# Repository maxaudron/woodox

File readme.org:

#+title: Readme

* Decisions
** MUX controll central vs seperate
We can either control each mux on it's own, taking up significantly more pins
or have them be controlled all at the same time

- Much simpler routing
- less traces

- customize matrix scanning

** Split vs Lefty logic
either controller on each hand, or controller only on one hand

*** Split
- can use more mux
- lower latency?
- more keys
- mirror PCB

CD74HC4051
  
*** Lefty
- less cost
- simpler?
- analog signals over longer wire
  - potential interference?

- sepperate PCB designs
  
* TODOs
** TODO connect mux com only to uneven GPIO pins for PWM input
** DONE add pull up resistors to mux com
** DONE adjust value of drv5057
A3 uses ~25% of the messuring range in one direction
A2 would use ~50%
A1 would use 100%, but might clip.
** DONE switch to drv5056A2
** TODO Use same pins for all mux selects
** TODO matrix to keycode conversion
** TODO usb hid impl
https://github.com/dlkj/usbd-human-interface-device

* Magnet distance lookup table
3.25V VCC
3.00V @ 2.25mm = 24.12mT
0.95V @ 6.25mm =  3.52mT

#+begin_src python :python3.10 :results output
import math

R = 1.75
D = 4
z = 2.25
r = 24.12
B = - ( (2*r) / ( ( z / math.sqrt( (R**2) + (z**2) )) - ( (D+z) / math.sqrt( (R**2) + ((D+z)**2) ) ) ) )
print(B)
#+end_src

#+RESULTS:
: 277.8612937046934

** lookup table
#+begin_src python :python python3.10 :results output
import math
import numpy as np

Z = np.linspace(0.1, 10, 100)
B = 0.38
R = 1.75
D = 4

def flux(z):
    return (((B/2)*( ( (D+z) / math.sqrt((R**2) + ((D+z)**2)) )  -  ( z / math.sqrt((R**2)+(z**2)) )))*1000)

def voltage(x):
    return (600 + x * (100))

def value(x):
    return x / (3300.0 / 256.0)

flux_vec = np.vectorize(flux)
voltage_vec = np.vectorize(voltage)
value_vec = np.vectorize(value)

prev = 0
for z in Z:
    z = round(z, 2)
    y = float(flux_vec(z))
    v = float(voltage_vec(y))
    value = float(value_vec(v))
    value = round(value)
    print(str(value) + "..=" + str(prev-1) + " => " + str(int(z * 10)) + ",")
    prev = value
#+end_src

#+RESULTS:
#+begin_example
1318..=-1 => 1,
1240..=1317 => 2,
1163..=1239 => 3,
1088..=1162 => 4,
1015..=1087 => 5,
946..=1014 => 6,
880..=945 => 7,
819..=879 => 8,
761..=818 => 9,
706..=760 => 10,
656..=705 => 11,
610..=655 => 12,
567..=609 => 13,
528..=566 => 14,
492..=527 => 15,
459..=491 => 16,
429..=458 => 17,
401..=428 => 18,
375..=400 => 19,
352..=374 => 20,
331..=351 => 21,
312..=330 => 22,
294..=311 => 23,
277..=293 => 24,
262..=276 => 25,
248..=261 => 26,
236..=247 => 27,
224..=235 => 28,
213..=223 => 29,
203..=212 => 30,
194..=202 => 31,
186..=193 => 32,
178..=185 => 33,
170..=177 => 34,
164..=169 => 35,
157..=163 => 36,
151..=156 => 37,
146..=150 => 38,
141..=145 => 39,
136..=140 => 40,
132..=135 => 41,
127..=131 => 42,
124..=126 => 43,
120..=123 => 44,
116..=119 => 45,
113..=115 => 46,
110..=112 => 47,
107..=109 => 48,
105..=106 => 49,
102..=104 => 50,
100..=101 => 51,
98..=99 => 52,
95..=97 => 53,
93..=94 => 54,
92..=92 => 55,
90..=91 => 56,
88..=89 => 57,
86..=87 => 58,
85..=85 => 59,
83..=84 => 60,
82..=82 => 61,
81..=81 => 62,
79..=80 => 63,
78..=78 => 64,
77..=77 => 65,
76..=76 => 66,
75..=75 => 67,
74..=74 => 68,
73..=73 => 69,
72..=72 => 70,
71..=71 => 71,
71..=70 => 72,
70..=70 => 73,
69..=69 => 74,
68..=68 => 75,
68..=67 => 76,
67..=67 => 77,
66..=66 => 78,
66..=65 => 79,
65..=65 => 80,
65..=64 => 81,
64..=64 => 82,
64..=63 => 83,
63..=63 => 84,
63..=62 => 85,
62..=62 => 86,
62..=61 => 87,
61..=61 => 88,
61..=60 => 89,
60..=60 => 90,
60..=59 => 91,
60..=59 => 92,
59..=59 => 93,
59..=58 => 94,
59..=58 => 95,
58..=58 => 96,
58..=57 => 97,
58..=57 => 98,
58..=57 => 99,
57..=57 => 100,
#+end_example

** graph
#+NAME: magnets
|       B |    R | D |
|---------+------+---|
|    0.38 | 1.75 | 4 |
|    0.28 | 1.75 | 4 |

#+begin_src python :python python3.10 :results file :exports both :var data=magnets
import math
import matplotlib.pyplot as plt
import numpy as np

for line in data:
    Z = np.linspace(0.1, 10, 100)
    B = line[0]
    R = line[1]
    D = line[2]

    def f(z):
        r = (((B/2)*( ( (D+z) / math.sqrt((R**2) + ((D+z)**2)) )  -  ( z / math.sqrt((R**2)+(z**2)) )))*1000)
        if z == 2.0:
            plt.annotate('A=' + str(z) + "," + str(round(r, 2)), xy=(z, r), xytext=(z+1, r+1))
        if z == 6.3:
            plt.annotate('B=' + str(z) + "," + str(round(r, 2)), xy=(z, r), xytext=(z+1, r+1))
        return r

    x = np.vectorize(f)
    plt.plot(Z, x(Z), label="B = " + str(B))

plt.xlabel("mm")
plt.ylabel("mT")
plt.legend()
filename = "plot.png"
plt.savefig(filename)
return(filename)
#+end_src

#+RESULTS:
[[file:plot.png]]

* Parts
LED Controller https://jlcpcb.com/partdetail/3305937-IS31FL3741A_QFLS4TR/C2940604

Multiplexer https://www.ti.com/lit/ds/symlink/cd74hc4067.pdf

Example rp2040 usage https://proto-pic.co.uk/content/RPI-PICO-R3-PUBLIC-SCHEMATIC.pdf

rp2040 https://datasheets.raspberrypi.com/rp2040/rp2040-datasheet.pdf

** Hall Sensor
https://www.ti.com/sensors/magnetic-sensors/linear-hall-effect-sensors/overview.html

DRV5055A3 SOT-23
https://www.ti.com/lit/ds/symlink/drv5055.pdf?ts=1672207827147&ref_url=https%253A%252F%252Fwww.ti.com%252Fproduct%252FDRV5055%252Fpart-details%252FDRV5055A1QLPG

35 keys per side

DRV5057
https://www.ti.com/lit/ds/symlink/drv5057.pdf?ts=1672321537787&ref_url=https%253A%252F%252Fwww.ti.com%252Fsensors%252Fmagnetic-sensors%252Flinear-hall-effect-sensors%252Fproducts.html

https://www.digikey.de/en/product-highlight/s/sunled/reverse-mount-rgb-plcc-smd-led

13,200 Gauss
1320mT

3.5mm diameter x 4 thiccness
z from 2.25mm to 6.25mm

Divide[13200,2](Divide[D + 4mm,Sqrt[Power[\(40)0.5 * 3.5mm\(41),2]+ \(40)D + 4mm\(41)]] - Divide[D,Sqrt[Power[\(40)0.5 * 3.5mm\(41),2]+ Power[D,2]]])

#+begin_src gnuplot
B = 1480
C = 4.7625
T = 12.7

plot [D = -20 :20] (B/2)*( ( ( D + T ) / sqrt( (0.5*C)**2 + (D+T)**2 ) ) - ( D / sqrt(0.5*C)**2 + D**2 ) )
#+end_src

https://crocus-technology.com/basic-magnetic-field-calculator/

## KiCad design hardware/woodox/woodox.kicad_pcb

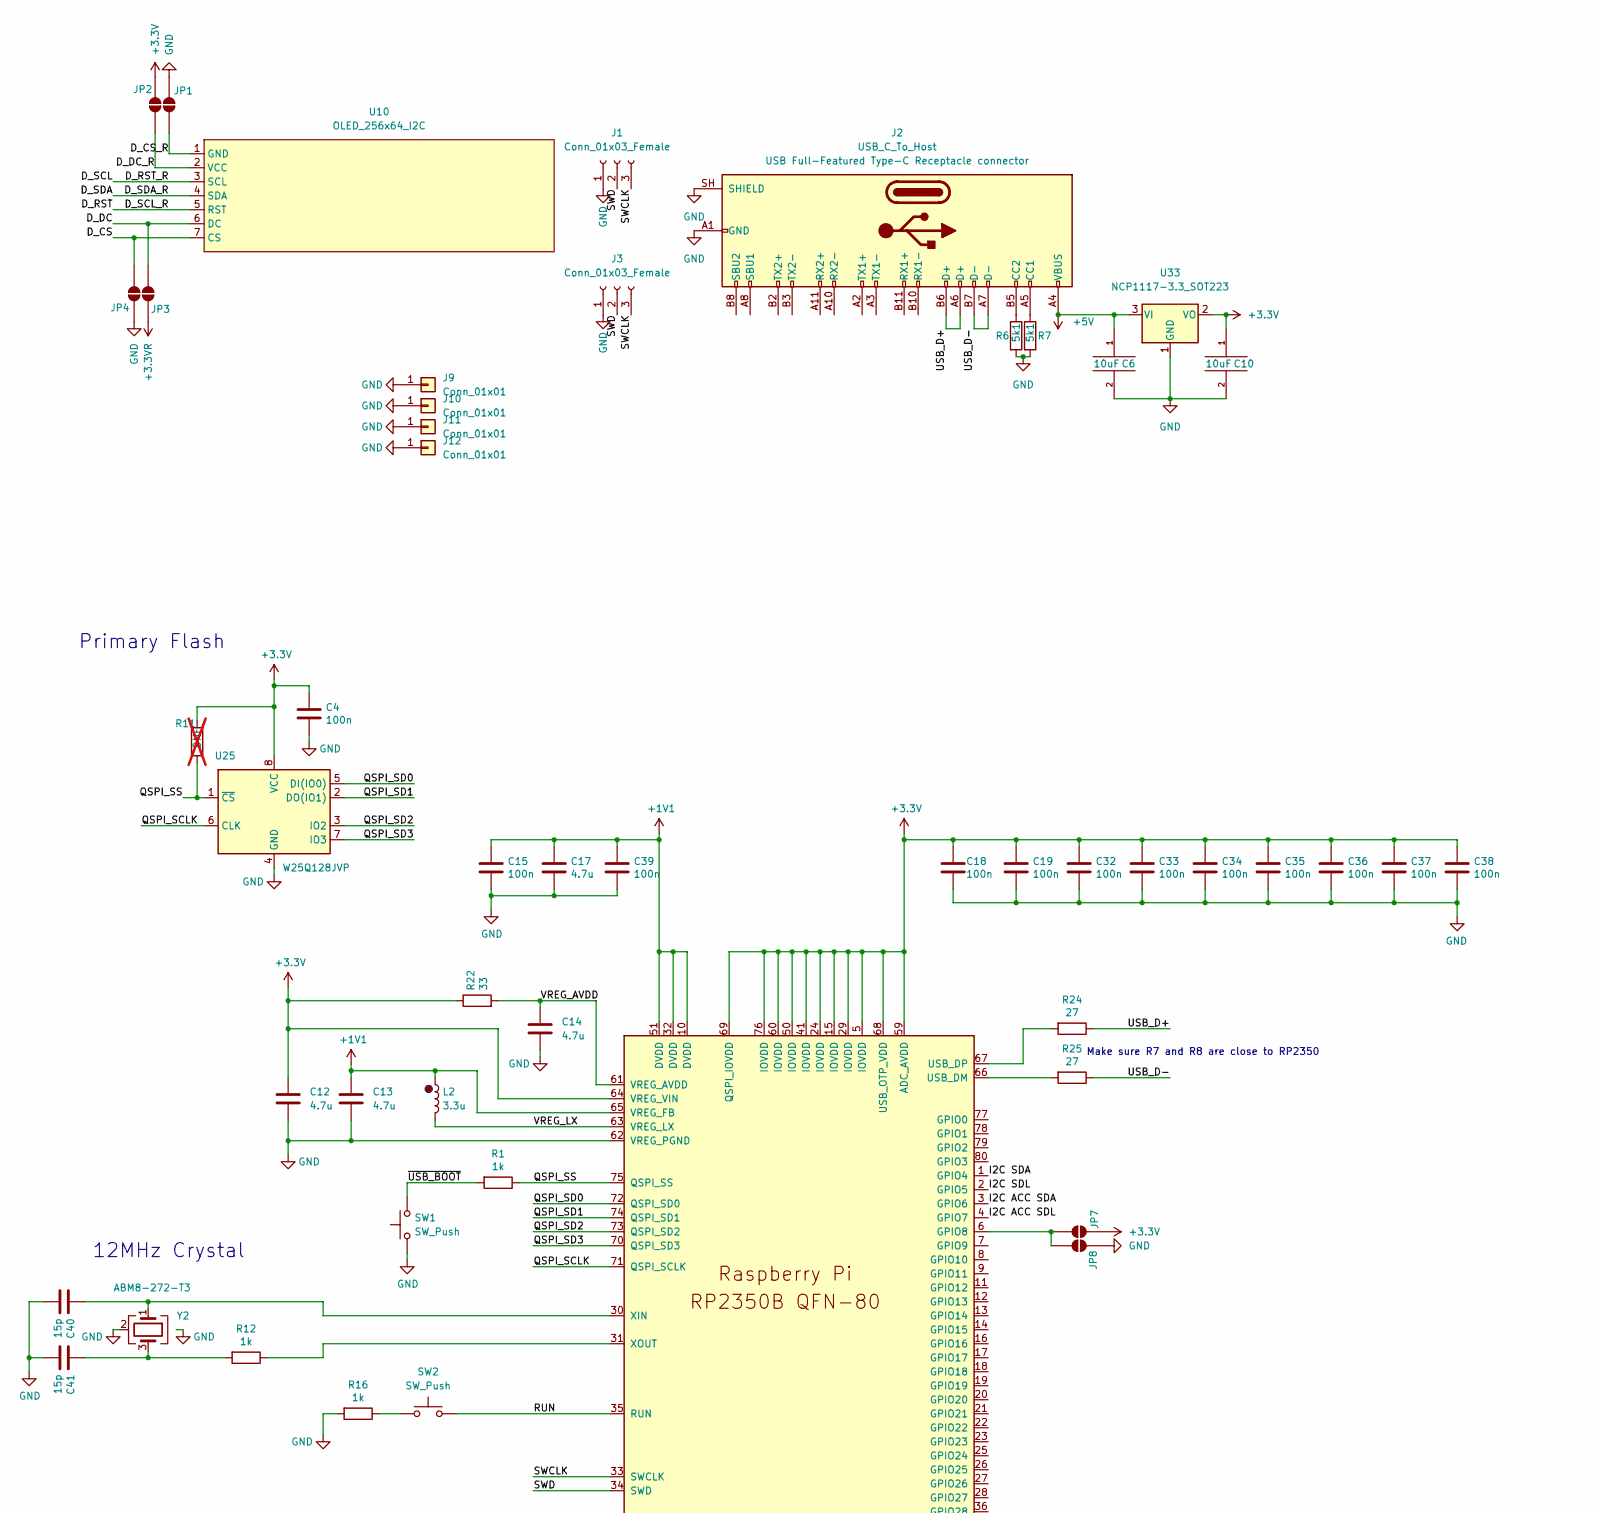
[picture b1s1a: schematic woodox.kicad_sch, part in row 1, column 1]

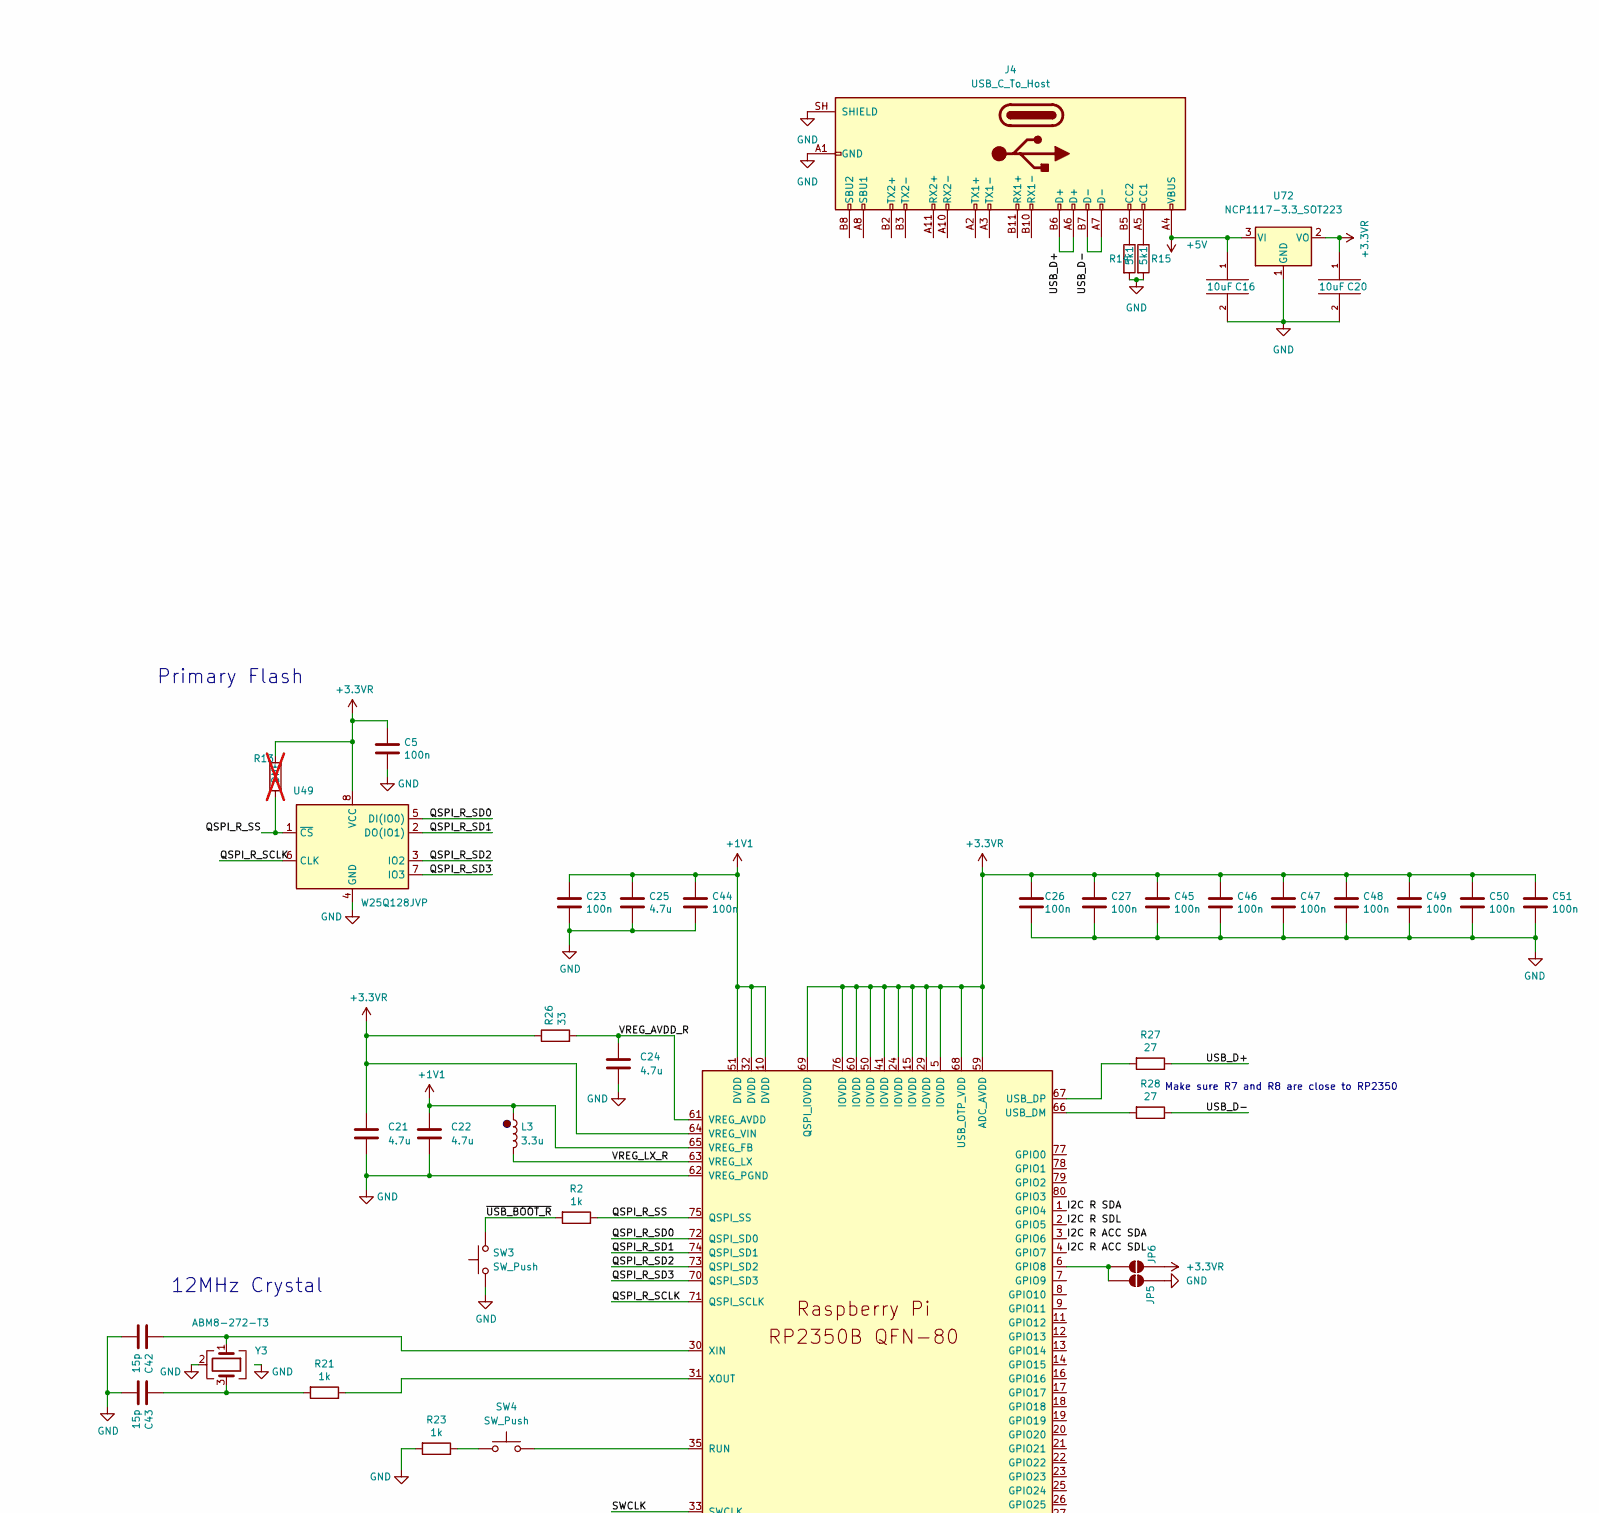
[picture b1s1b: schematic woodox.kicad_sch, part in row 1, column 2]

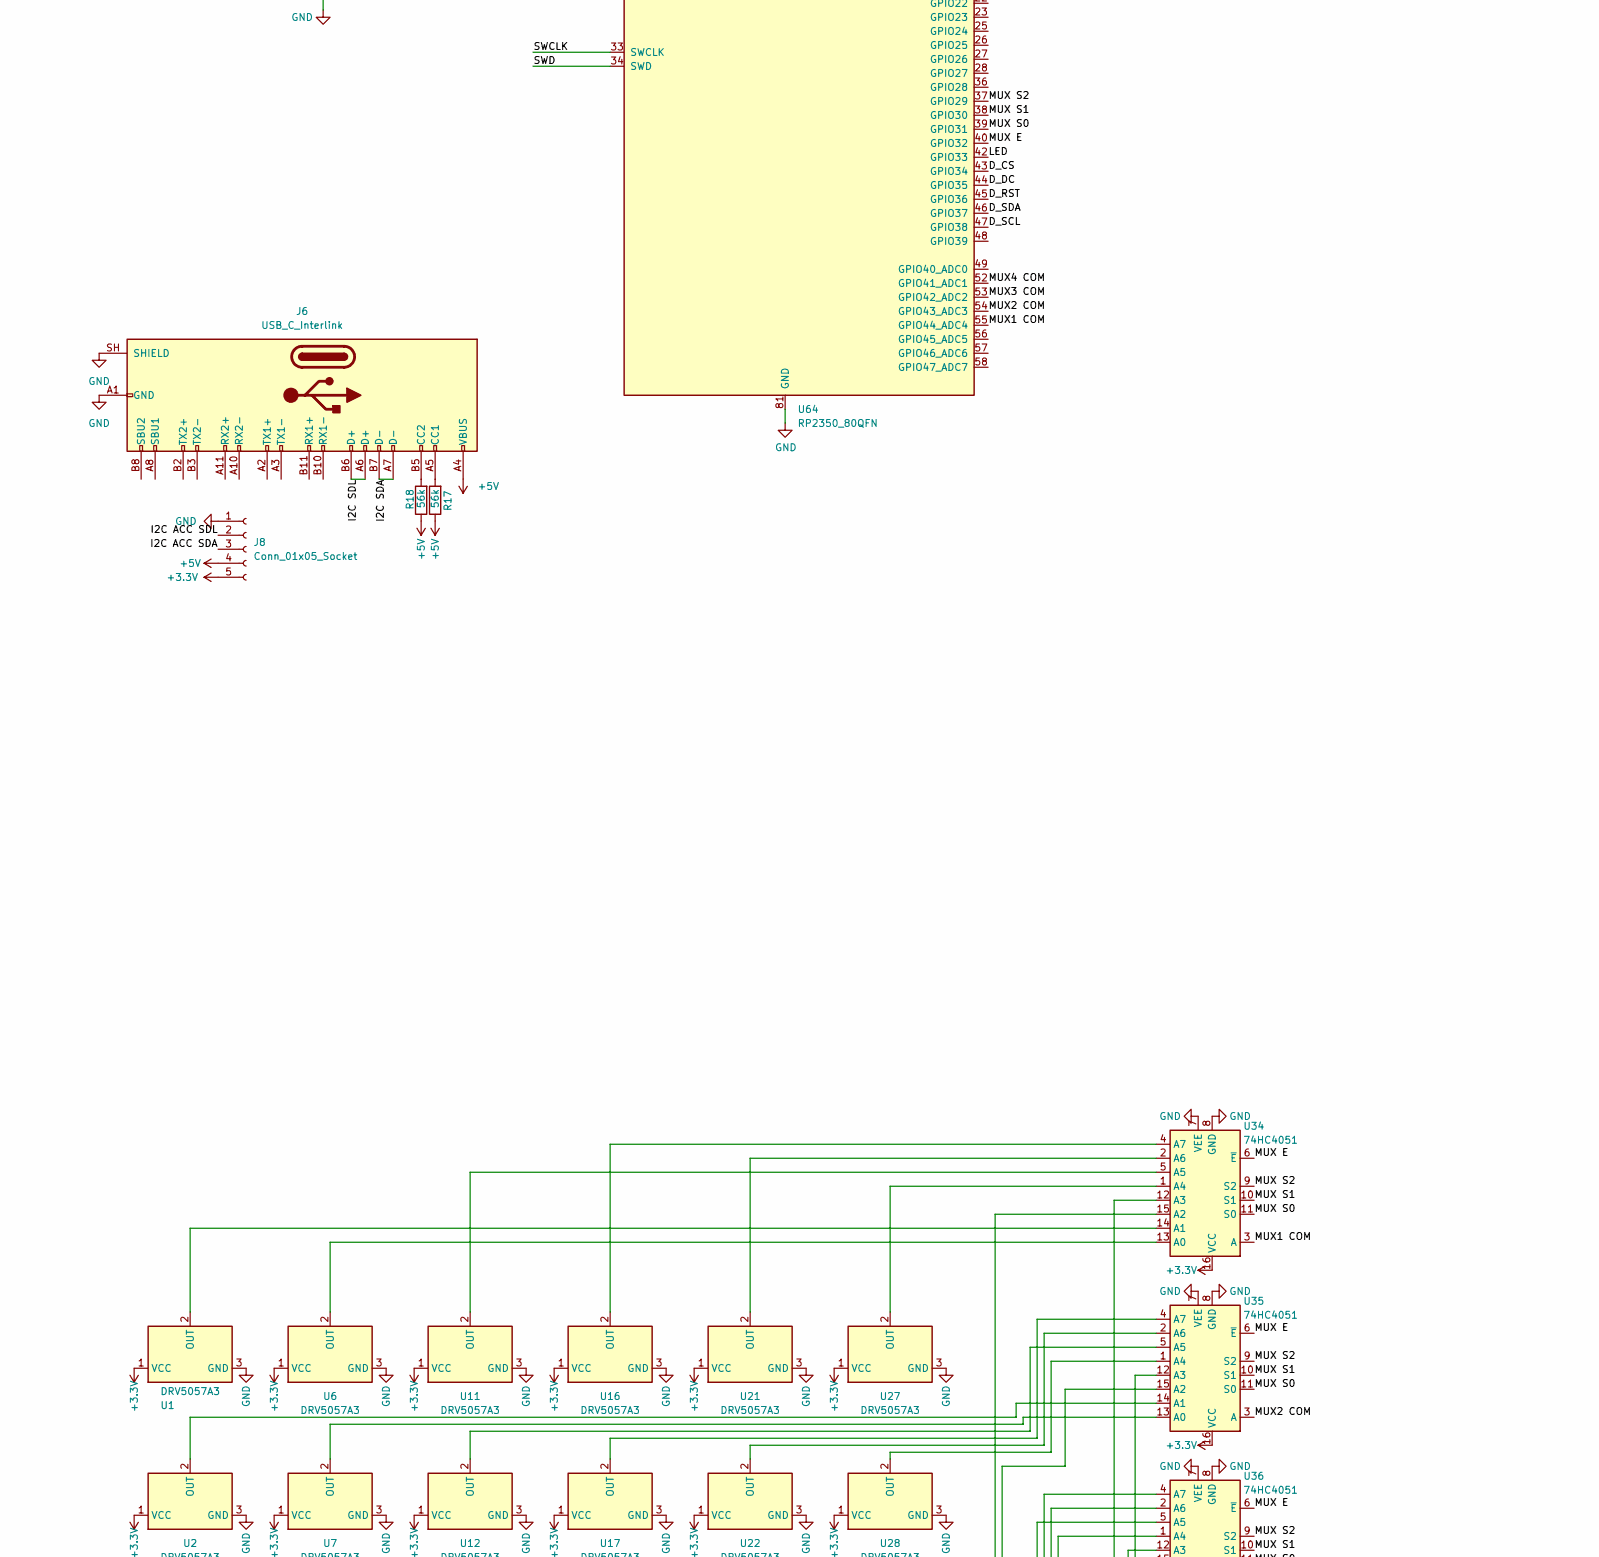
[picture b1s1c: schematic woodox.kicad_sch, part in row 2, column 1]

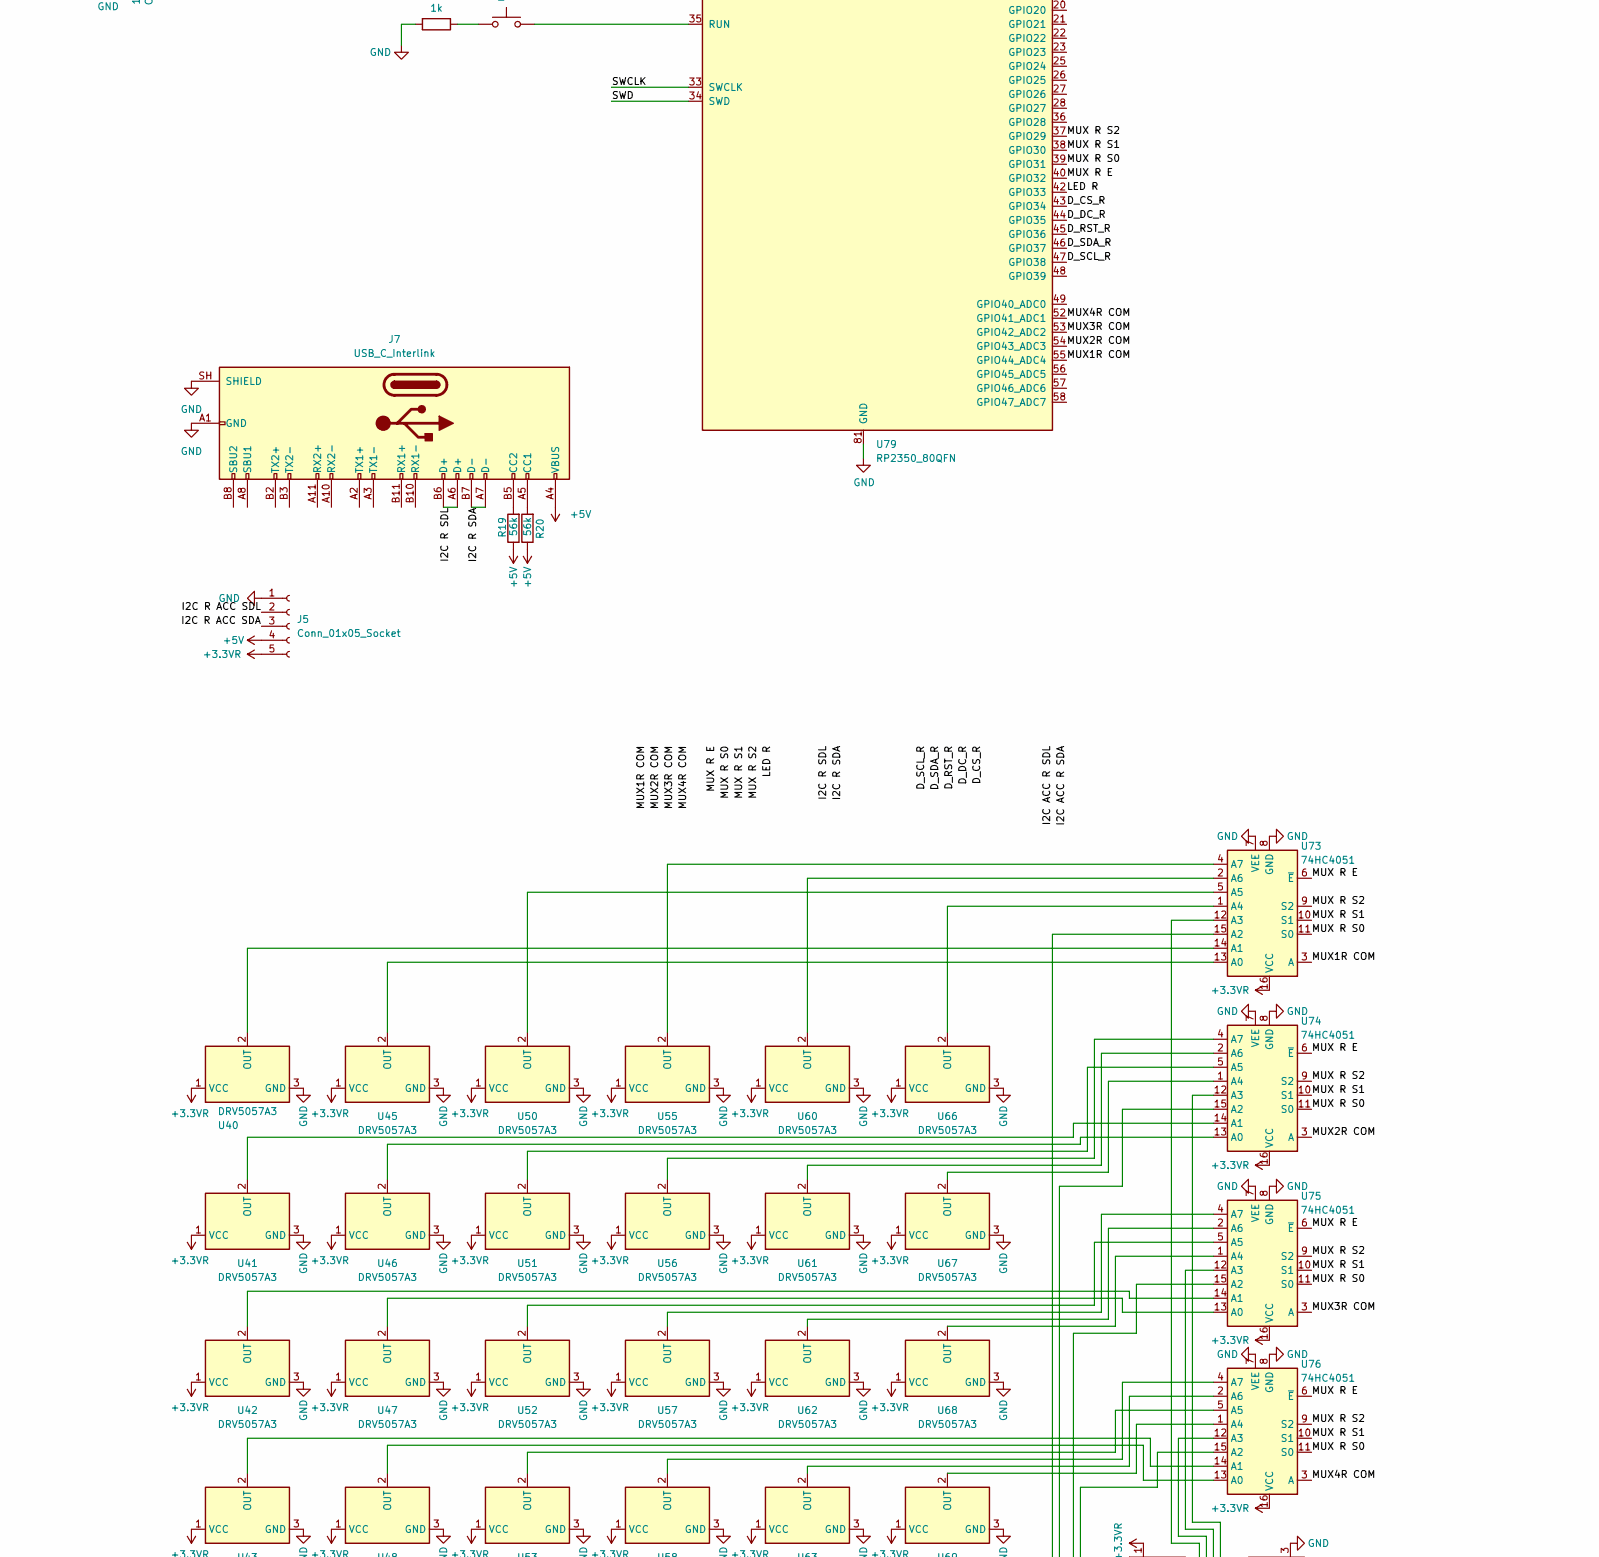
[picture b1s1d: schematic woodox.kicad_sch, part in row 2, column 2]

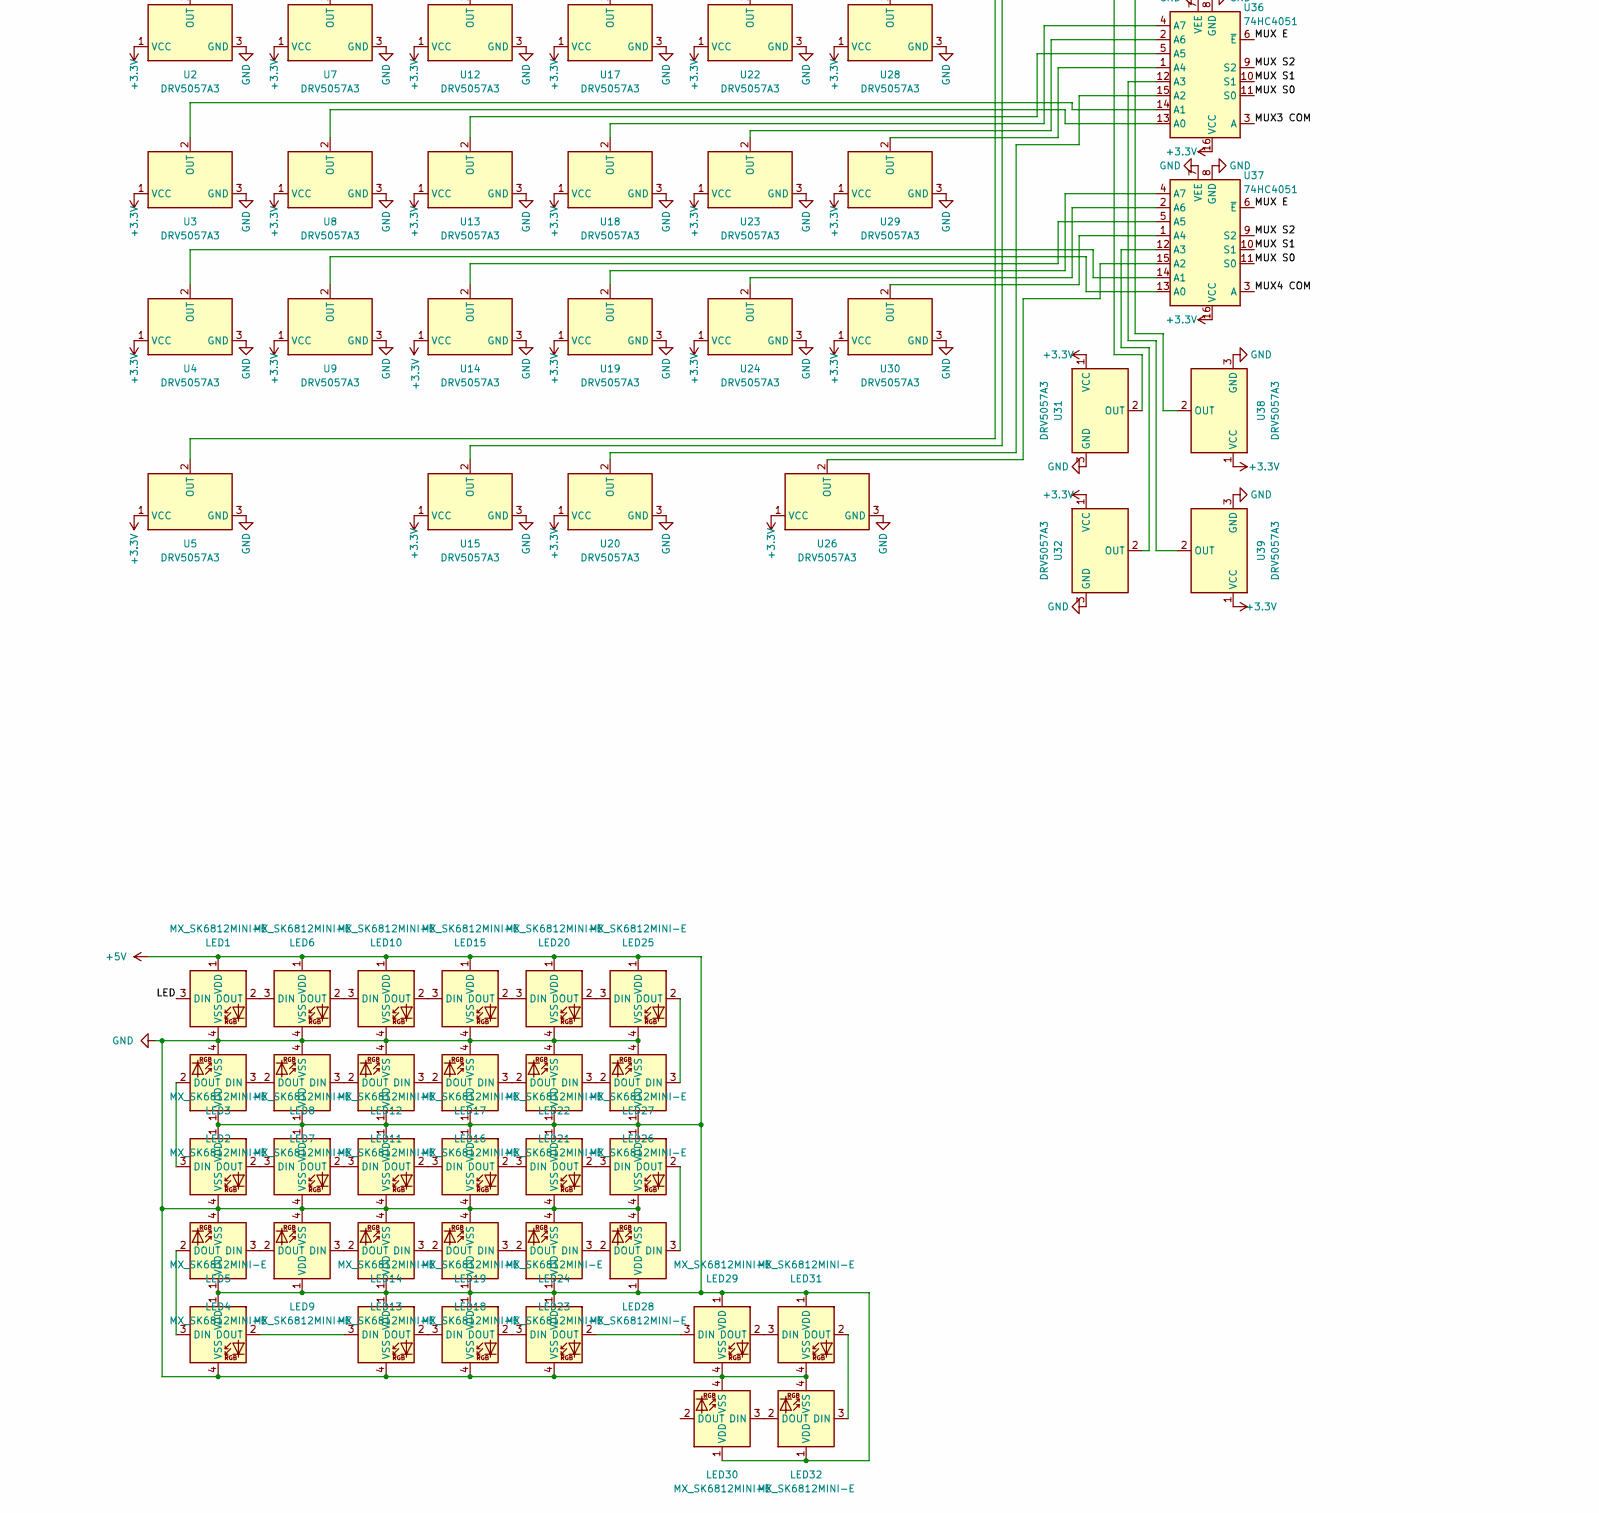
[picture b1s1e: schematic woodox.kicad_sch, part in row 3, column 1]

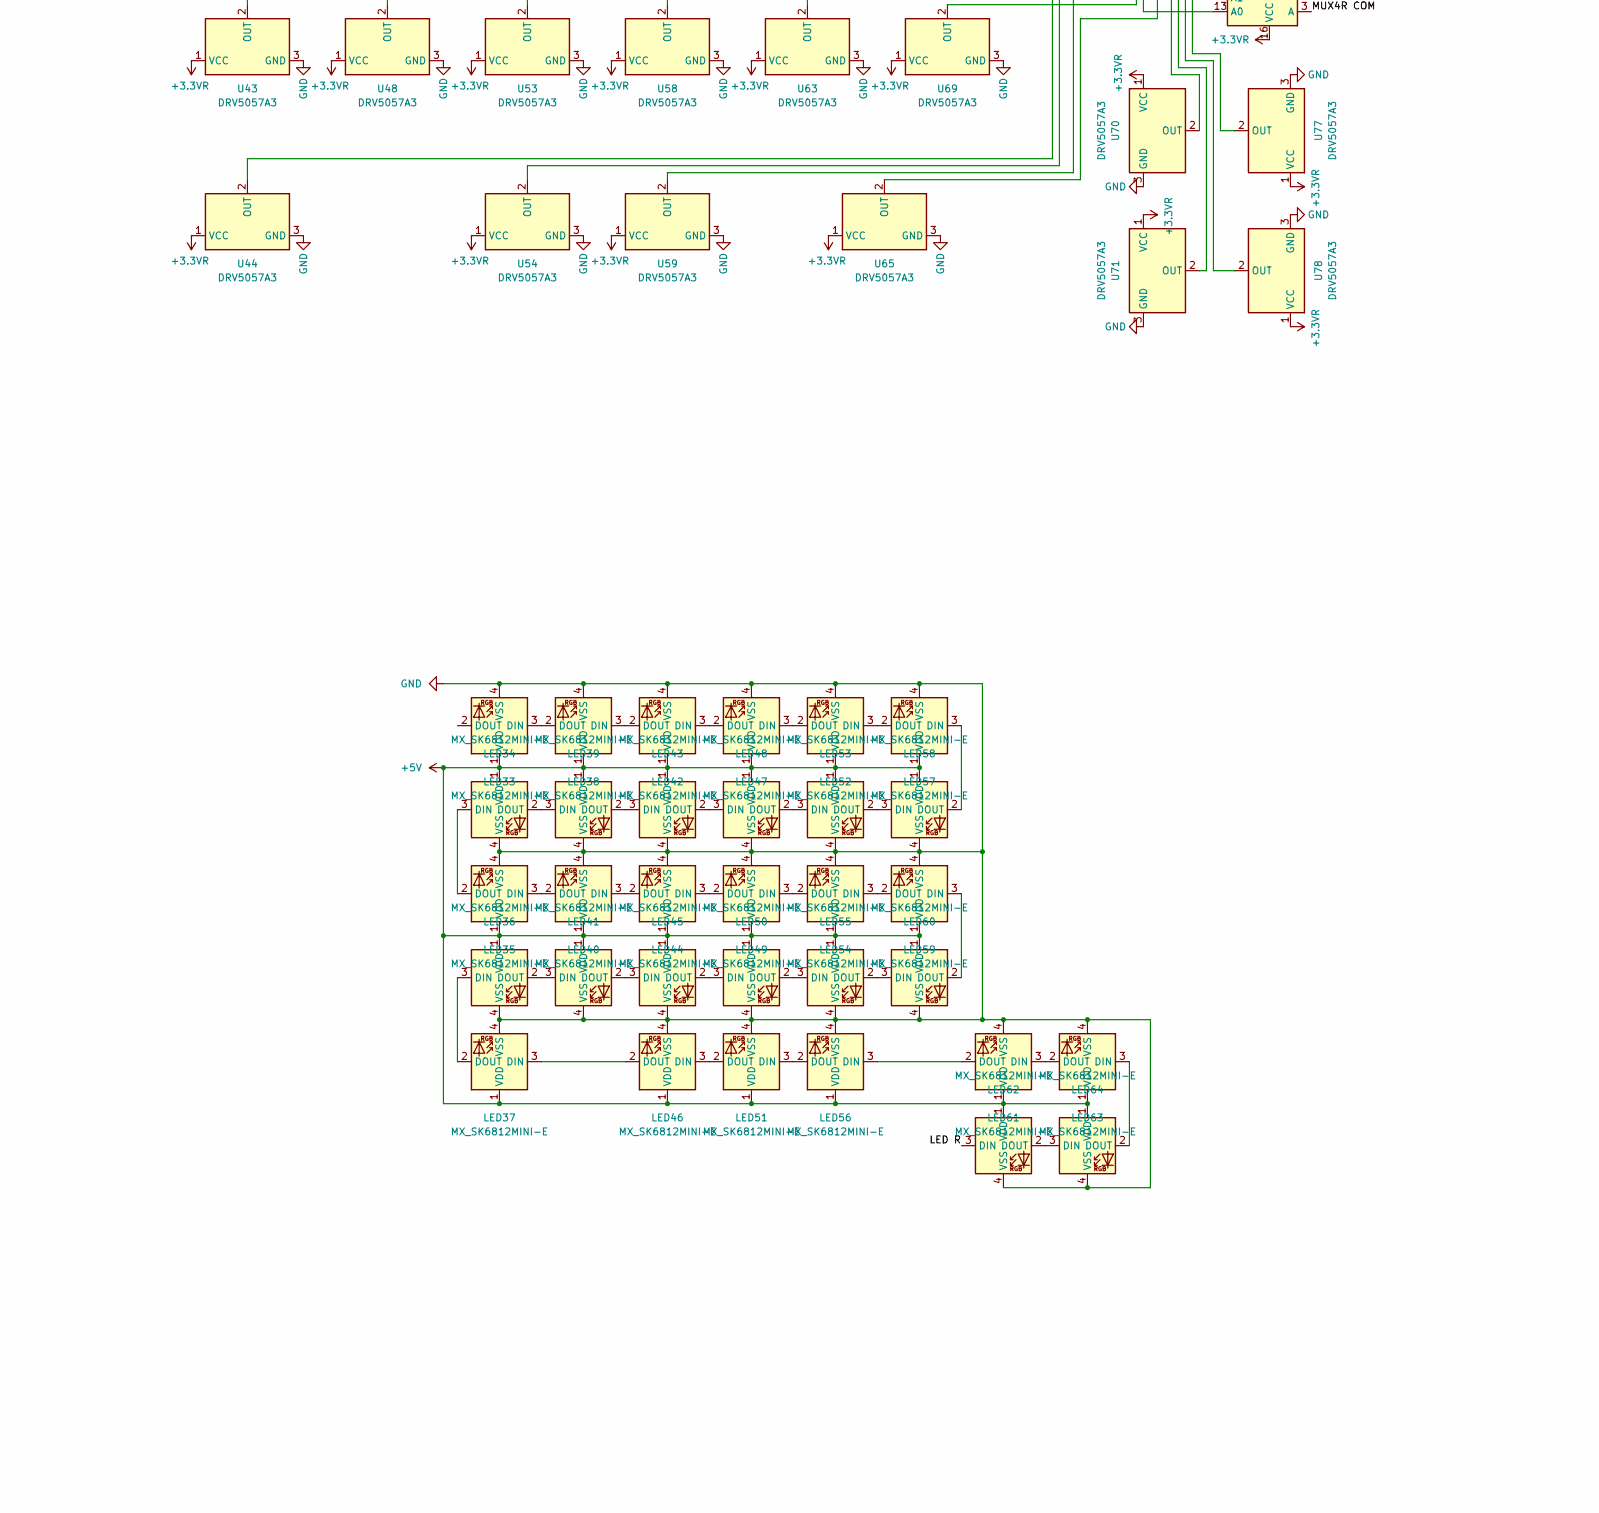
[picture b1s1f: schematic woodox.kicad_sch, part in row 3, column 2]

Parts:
C4, C5, C15, C18, C19, C23, C26, C27, C32, C33, C34, C35, C36, C37, C38, C39, C44, C45, C46, C47, C48, C49, C50, C51: 100n; C_0402_1005Metric
C6, C10, C16, C20: 10uF; C_0402_1005Metric; MPN GRM155R60J106ME15D
C12, C13, C21, C22: 4.7u; C_0402_1005Metric_small_pads
C14, C17, C24, C25: 4.7u; C_0402_1005Metric
C40, C41, C42, C43: 15p; C_0402_1005Metric
J1, J3: Conn_01x03_Female; TestPad_3pins; MPN HEADER
J2, J4: USB_C_To_Host; USB_C_Receptacle_Amphenol_12401610E4-2A; MPN 12401832E402A
J5, J8: Conn_01x05_Socket; TestPad_5pins
J6, J7: USB_C_Interlink; USB_C_Receptacle_Amphenol_12401610E4-2A; MPN 12401832E402A
J9, J10, J11, J12: Conn_01x01; MountingHole_3.2mm_M3_DIN965_Pad
JP1, JP2, JP3, JP4, JP5, JP6, JP7, JP8: SolderJumper_2_Open; SolderJumper-2_P1.3mm_Open_Pad1.0x1.5mm
L2, L3: 3.3u; L_pol_2016; MPN AOTA-B201610S3R3-101-T
LED1, LED2, LED3, LED4, LED5, LED6, LED7, LED8, LED9, LED10, LED11, LED12, LED13, LED14, LED15, LED16, LED17, LED18, LED19, LED20, LED21, LED22, LED23, LED24, LED25, LED26, LED27, LED28, LED29, LED30, LED31, LED32, LED33, LED34, LED35, LED36, LED37, LED38, LED39, LED40, LED41, LED42, LED43, LED44, LED45, LED46, LED47, LED48, LED49, LED50, LED51, LED52, LED53, LED54, LED55, LED56, LED57, LED58, LED59, LED60, LED61, LED62, LED63, LED64: MX_SK6812MINI-E; LED_MX_SK6812MINI-R; MPN SK6812MINI-E
R1, R2, R12, R16, R21, R23: 1k; R_0402_1005Metric
R6, R7, R14, R15: 5k1; R_0402_1005Metric; MPN ERJ-3EKF5101V
R11, R13: DNF; R_0402_1005Metric; MPN ERJ-3EKF1002V; not fitted
R17, R18, R19, R20: 56k; R_0402_1005Metric; MPN ERJ-3EKF1002V
R22, R26: 33; R_0402_1005Metric
R24, R25, R27, R28: 27; R_0402_1005Metric
SW1, SW2, SW3, SW4: SW_Push; SW_Push_1P1T_NO_Vertical_Wuerth_434133025816
U1, U2, U3, U4, U5, U6, U7, U8, U9, U11, U12, U13, U14, U15, U16, U17, U18, U19, U20, U21, U22, U23, U24, U26, U27, U28, U29, U30, U31, U32, U38, U39, U40, U41, U42, U43, U44, U45, U46, U47, U48, U50, U51, U52, U53, U54, U55, U56, U57, U58, U59, U60, U61, U62, U63, U65, U66, U67, U68, U69, U70, U71, U77, U78: DRV5057A3; DRV505x; MPN DRV5057A3
U10: OLED_256x64_I2C; MPN HEADER
U25, U49: W25Q128JVP; WSON-8-1EP_6x5mm_P1.27mm_EP3.4x4.3mm
U33, U72: NCP1117-3.3_SOT223; SOT-223-3_TabPin2; MPN NCP1117LPST33T3G
U34, U35, U36, U37, U73, U74, U75, U76: 74HC4051; TSSOP-16_4.4x5mm_P0.65mm; MPN CD74HC4051PWR
U64, U79: RP2350_80QFN; RP2350-QFN-80-1EP_10x10_P0.4mm_EP3.4x3.4mm_ThermalVias
Y2, Y3: ABM8-272-T3; Crystal_SMD_3225-4Pin_3.2x2.5mm

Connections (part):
+1V1: C13.1, C15.1, C17.1, C22.1, C23.1, C25.1, C39.1, C44.1, L2.1, L3.1, U64.10 (DVDD), U64.32 (DVDD), U64.51 (DVDD), U64.65 (VREG_FB), U79.10 (DVDD), U79.32 (DVDD), U79.51 (DVDD), U79.65 (VREG_FB)
+3.3V: C4.1, C10.1, C12.1, C18.1, C19.1, C32.1, C33.1, C34.1, C35.1, C36.1, C37.1, C38.1, J8.5, JP2.2 (B), JP7.2 (B), R11.2, R22.1, U1.1 (VCC), U2.1 (VCC), U3.1 (VCC), U4.1 (VCC), U5.1 (VCC), U6.1 (VCC), U7.1 (VCC), U8.1 (VCC), U9.1 (VCC), U11.1 (VCC), U12.1 (VCC), U13.1 (VCC), U14.1 (VCC), U15.1 (VCC), U16.1 (VCC), U17.1 (VCC), U18.1 (VCC), U19.1 (VCC), U20.1 (VCC), U21.1 (VCC), U22.1 (VCC), U23.1 (VCC), U24.1 (VCC), U25.8 (VCC), U26.1 (VCC), U27.1 (VCC), U28.1 (VCC), U29.1 (VCC), U30.1 (VCC), U31.1 (VCC), U32.1 (VCC), U33.2 (VO), U34.16 (VCC), U35.16 (VCC), U36.16 (VCC), U37.16 (VCC), U38.1 (VCC), U39.1 (VCC), U64.5 (IOVDD), U64.15 (IOVDD), U64.24 (IOVDD), U64.29 (IOVDD), U64.41 (IOVDD), U64.50 (IOVDD), U64.59 (ADC_AVDD), U64.60 (IOVDD), U64.64 (VREG_VIN), U64.68 (USB_OTP_VDD), U64.69 (QSPI_IOVDD), U64.76 (IOVDD)
+3.3VR: C5.1, C20.1, C21.1, C26.1, C27.1, C45.1, C46.1, C47.1, C48.1, C49.1, C50.1, C51.1, J5.5, JP3.2 (B), JP6.2 (B), R13.2, R26.1, U40.1 (VCC), U41.1 (VCC), U42.1 (VCC), U43.1 (VCC), U44.1 (VCC), U45.1 (VCC), U46.1 (VCC), U47.1 (VCC), U48.1 (VCC), U49.8 (VCC), U50.1 (VCC), U51.1 (VCC), U52.1 (VCC), U53.1 (VCC), U54.1 (VCC), U55.1 (VCC), U56.1 (VCC), U57.1 (VCC), U58.1 (VCC), U59.1 (VCC), U60.1 (VCC), U61.1 (VCC), U62.1 (VCC), U63.1 (VCC), U65.1 (VCC), U66.1 (VCC), U67.1 (VCC), U68.1 (VCC), U69.1 (VCC), U70.1 (VCC), U71.1 (VCC), U72.2 (VO), U73.16 (VCC), U74.16 (VCC), U75.16 (VCC), U76.16 (VCC), U77.1 (VCC), U78.1 (VCC), U79.5 (IOVDD), U79.15 (IOVDD), U79.24 (IOVDD), U79.29 (IOVDD), U79.41 (IOVDD), U79.50 (IOVDD), U79.59 (ADC_AVDD), U79.60 (IOVDD), U79.64 (VREG_VIN), U79.68 (USB_OTP_VDD), U79.69 (QSPI_IOVDD), U79.76 (IOVDD)
+5V: C6.1, C16.1, J2.A4 (VBUS), J2.A9 (VBUS), J2.B4 (VBUS), J2.B9 (VBUS), J4.A4 (VBUS), J4.A9 (VBUS), J4.B4 (VBUS), J4.B9 (VBUS), J5.4, J6.A4 (VBUS), J6.A9 (VBUS), J6.B4 (VBUS), J6.B9 (VBUS), J7.A4 (VBUS), J7.A9 (VBUS), J7.B4 (VBUS), J7.B9 (VBUS), J8.4, LED1.1 (VDD), LED2.1 (VDD), LED3.1 (VDD), LED4.1 (VDD), LED5.1 (VDD), LED6.1 (VDD), LED7.1 (VDD), LED8.1 (VDD), LED9.1 (VDD), LED10.1 (VDD), LED11.1 (VDD), LED12.1 (VDD), LED13.1 (VDD), LED14.1 (VDD), LED15.1 (VDD), LED16.1 (VDD), LED17.1 (VDD), LED18.1 (VDD), LED19.1 (VDD), LED20.1 (VDD), LED21.1 (VDD), LED22.1 (VDD), LED23.1 (VDD), LED24.1 (VDD), LED25.1 (VDD), LED26.1 (VDD), LED27.1 (VDD), LED28.1 (VDD), LED29.1 (VDD), LED30.1 (VDD), LED31.1 (VDD), LED32.1 (VDD), LED33.1 (VDD), LED34.1 (VDD), LED35.1 (VDD), LED36.1 (VDD), LED37.1 (VDD), LED38.1 (VDD), LED39.1 (VDD), LED40.1 (VDD), LED41.1 (VDD), LED42.1 (VDD), LED43.1 (VDD), LED44.1 (VDD), LED45.1 (VDD), LED46.1 (VDD), LED47.1 (VDD), LED48.1 (VDD), LED49.1 (VDD), LED50.1 (VDD), LED51.1 (VDD), LED52.1 (VDD), LED53.1 (VDD), LED54.1 (VDD), LED55.1 (VDD), LED56.1 (VDD), LED57.1 (VDD), LED58.1 (VDD), LED59.1 (VDD), LED60.1 (VDD)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
/D_CS: JP4.1 (A), U10.7 (CS), U64.43 (GPIO34)
/D_CS_R: JP1.1 (A), U10.1 (GND), U79.43 (GPIO34)
/D_DC: JP3.1 (A), U10.6 (DC), U64.44 (GPIO35)
/D_DC_R: JP2.1 (A), U10.2 (VCC), U79.44 (GPIO35)
/D_RST: U10.5 (RST), U64.45 (GPIO36), U79.47 (GPIO38)
/D_RST_R: U10.3 (SCL), U64.47 (GPIO38), U79.45 (GPIO36)
/D_SDA: U10.4 (SDA), U64.46 (GPIO37), U79.46 (GPIO37)
/I2C ACC SDA: J8.3, U64.3 (GPIO6)
/I2C ACC SDL: J8.2, U64.4 (GPIO7)
/I2C R ACC SDA: J5.3, U79.3 (GPIO6)
/I2C R ACC SDL: J5.2, U79.4 (GPIO7)
/I2C R SDA: J7.A7 (D-), J7.B7 (D-), U79.1 (GPIO4)
/I2C R SDL: J7.A6 (D+), J7.B6 (D+), U79.2 (GPIO5)
/I2C SDA: J6.A7 (D-), J6.B7 (D-), U64.1 (GPIO4)
/I2C SDL: J6.A6 (D+), J6.B6 (D+), U64.2 (GPIO5)
/LED: LED1.3 (DIN), U64.42 (GPIO33)
/LED R: LED62.3 (DIN), U79.42 (GPIO33)
/MUX1 COM: U34.3 (A), U64.55 (GPIO44_ADC4)
/MUX1R COM: U73.3 (A), U79.55 (GPIO44_ADC4)
/MUX2 COM: U35.3 (A), U64.54 (GPIO43_ADC3)
/MUX2R COM: U74.3 (A), U79.54 (GPIO43_ADC3)
/MUX3 COM: U36.3 (A), U64.53 (GPIO42_ADC2)
/MUX3R COM: U75.3 (A), U79.53 (GPIO42_ADC2)
/MUX4 COM: U37.3 (A), U64.52 (GPIO41_ADC1)
/MUX4R COM: U76.3 (A), U79.52 (GPIO41_ADC1)
/MUX E: U34.6 (~E), U35.6 (~E), U36.6 (~E), U37.6 (~E), U64.40 (GPIO32)
/MUX R E: U73.6 (~E), U74.6 (~E), U75.6 (~E), U76.6 (~E), U79.40 (GPIO32)
/MUX R S0: U73.11 (S0), U74.11 (S0), U75.11 (S0), U76.11 (S0), U79.39 (GPIO31)
/MUX R S1: U73.10 (S1), U74.10 (S1), U75.10 (S1), U76.10 (S1), U79.38 (GPIO30)
/MUX R S2: U73.9 (S2), U74.9 (S2), U75.9 (S2), U76.9 (S2), U79.37 (GPIO29)
/MUX S0: U34.11 (S0), U35.11 (S0), U36.11 (S0), U37.11 (S0), U64.39 (GPIO31)
/MUX S1: U34.10 (S1), U35.10 (S1), U36.10 (S1), U37.10 (S1), U64.38 (GPIO30)
/MUX S2: U34.9 (S2), U35.9 (S2), U36.9 (S2), U37.9 (S2), U64.37 (GPIO29)
/QSPI_R_SCLK: U49.6 (CLK), U79.71 (QSPI_SCLK)
/QSPI_R_SD0: U49.5 (DI(IO0)), U79.72 (QSPI_SD0)
/QSPI_R_SD1: U49.2 (DO(IO1)), U79.74 (QSPI_SD1)
/QSPI_R_SD2: U49.3 (IO2), U79.73 (QSPI_SD2)
/QSPI_R_SD3: U49.7 (IO3), U79.70 (QSPI_SD3)
/QSPI_R_SS: R2.1, R13.1, U49.1 (~CS), U79.75 (QSPI_SS)
/QSPI_SCLK: U25.6 (CLK), U64.71 (QSPI_SCLK)
/QSPI_SD0: U25.5 (DI(IO0)), U64.72 (QSPI_SD0)
/QSPI_SD1: U25.2 (DO(IO1)), U64.74 (QSPI_SD1)
/QSPI_SD2: U25.3 (IO2), U64.73 (QSPI_SD2)
/QSPI_SD3: U25.7 (IO3), U64.70 (QSPI_SD3)
/QSPI_SS: R1.1, R11.1, U25.1 (~CS), U64.75 (QSPI_SS)
/RUN: SW2.2, U64.35 (RUN)
/SWCLK: J1.3, J3.3, U64.33 (SWCLK), U79.33 (SWCLK)
/SWD: J1.2, J3.2, U64.34 (SWD), U79.34 (SWD)
/USB_D+: J2.A6 (D+), J2.B6 (D+), J4.A6 (D+), J4.B6 (D+), R24.1, R27.1
/USB_D-: J2.A7 (D-), J2.B7 (D-), J4.A7 (D-), J4.B7 (D-), R25.1, R28.1
/VREG_AVDD: C14.1, R22.2, U64.61 (VREG_AVDD)
/VREG_AVDD_R: C24.1, R26.2, U79.61 (VREG_AVDD)
/VREG_LX: L2.2, U64.63 (VREG_LX)
/VREG_LX_R: L3.2, U79.63 (VREG_LX)
/~USB_BOOT_R: R2.2, SW3.2
/~USB_BOOT: R1.2, SW1.2
GND: C4.2, C5.2, C6.2, C10.2, C12.2, C13.2, C14.2, C15.2, C16.2, C17.2, C18.2, C19.2, C20.2, C21.2, C22.2, C23.2, C24.2, C25.2, C26.2, C27.2, C32.2, C33.2, C34.2, C35.2, C36.2, C37.2, C38.2, C39.2, C40.2, C41.2, C42.2, C43.2, C44.2, C45.2, C46.2, C47.2, C48.2, C49.2, C50.2, C51.2, J1.1, J2.A1 (GND), J2.A12 (GND), J2.B1 (GND), J2.B12 (GND), J2.SH (SHIELD), J3.1, J4.A1 (GND), J4.A12 (GND), J4.B1 (GND), J4.B12 (GND), J4.SH (SHIELD), J5.1, J6.A1 (GND), J6.A12 (GND), J6.B1 (GND), J6.B12 (GND), J6.SH (SHIELD), J7.A1 (GND), J7.A12 (GND), J7.B1 (GND), J7.B12 (GND), J7.SH (SHIELD), J8.1, J9.1 (Pin_1_1), J10.1 (Pin_1_1), J11.1 (Pin_1_1), J12.1 (Pin_1_1), JP1.2 (B), JP4.2 (B), JP5.2 (B), JP8.2 (B), LED1.4 (VSS), LED2.4 (VSS), LED3.4 (VSS), LED4.4 (VSS), LED5.4 (VSS), LED6.4 (VSS), LED7.4 (VSS), LED8.4 (VSS)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
unnamed: C41.1, R12.2, Y2.3
unnamed: C43.1, R21.2, Y3.3
unnamed: J2.A5 (CC1), R7.1
unnamed: J2.B5 (CC2), R6.1
unnamed: J4.A5 (CC1), R15.1
unnamed: J4.B5 (CC2), R14.1
unnamed: J6.A5 (CC1), R17.2
unnamed: J6.B5 (CC2), R18.2
unnamed: J7.A5 (CC1), R20.2
unnamed: J7.B5 (CC2), R19.2
unnamed: JP5.1 (A), JP6.1 (A), U79.6 (GPIO8)
unnamed: JP7.1 (A), JP8.1 (A), U64.6 (GPIO8)
unnamed: LED1.2 (DOUT), LED6.3 (DIN)
unnamed: LED2.3 (DIN), LED7.2 (DOUT)
unnamed: LED2.2 (DOUT), LED3.3 (DIN)
unnamed: LED3.2 (DOUT), LED8.3 (DIN)
unnamed: LED4.3 (DIN), LED9.2 (DOUT)
unnamed: LED4.2 (DOUT), LED5.3 (DIN)
unnamed: LED6.2 (DOUT), LED10.3 (DIN)
unnamed: LED10.2 (DOUT), LED15.3 (DIN)
unnamed: LED11.3 (DIN), LED16.2 (DOUT)
unnamed: LED7.3 (DIN), LED11.2 (DOUT)
unnamed: LED8.2 (DOUT), LED12.3 (DIN)
unnamed: LED12.2 (DOUT), LED17.3 (DIN)
unnamed: LED13.3 (DIN), LED18.2 (DOUT)
unnamed: LED9.3 (DIN), LED13.2 (DOUT)
unnamed: LED5.2 (DOUT), LED14.3 (DIN)
unnamed: LED14.2 (DOUT), LED19.3 (DIN)
unnamed: LED15.2 (DOUT), LED20.3 (DIN)
unnamed: LED16.3 (DIN), LED21.2 (DOUT)
unnamed: LED17.2 (DOUT), LED22.3 (DIN)
unnamed: LED18.3 (DIN), LED23.2 (DOUT)
unnamed: LED19.2 (DOUT), LED24.3 (DIN)
unnamed: LED20.2 (DOUT), LED25.3 (DIN)
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
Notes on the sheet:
12MHz Crystal
Primary Flash
Make sure R7 and R8 are close to RP2350
